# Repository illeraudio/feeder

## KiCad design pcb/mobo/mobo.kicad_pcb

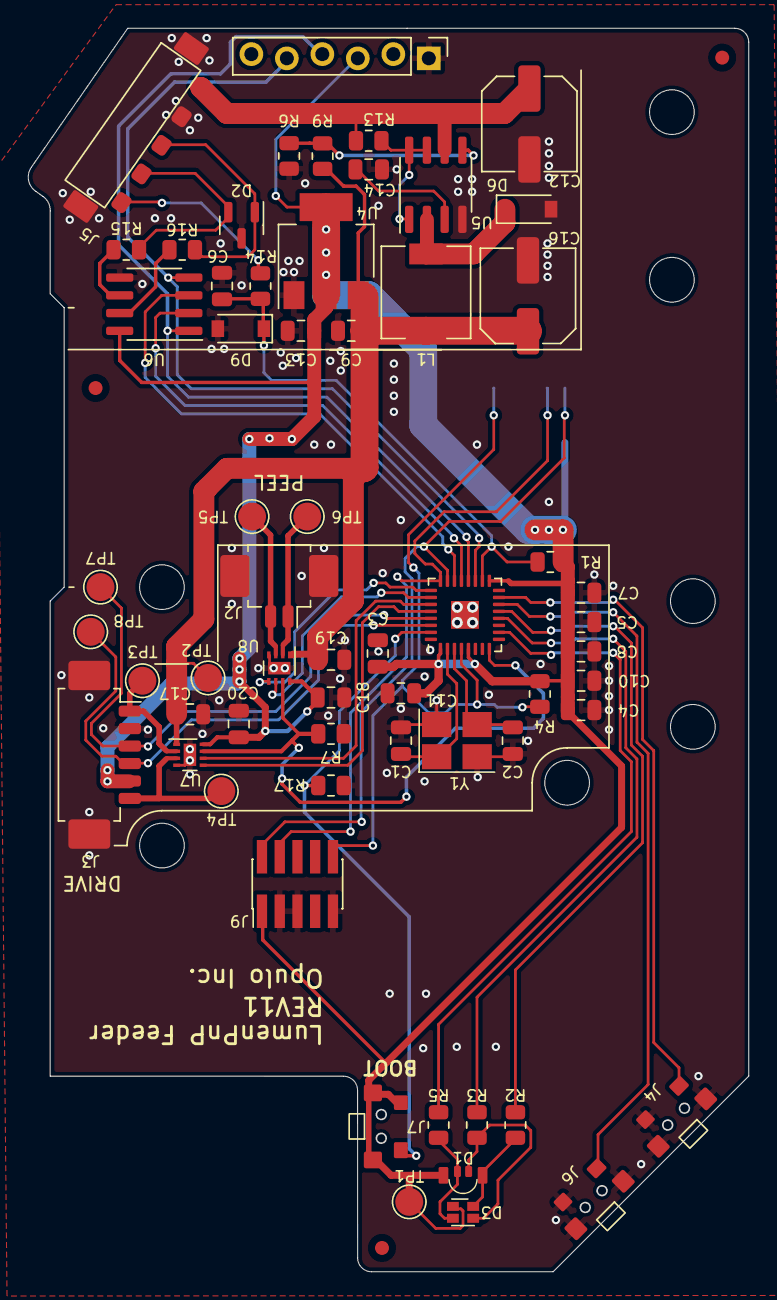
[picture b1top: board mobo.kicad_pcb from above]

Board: 2 copper layers, 51.6 x 89.0 mm, 65 parts (1 on the bottom side), 43 nets.

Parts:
C1, C2: 15p; C_0805_2012Metric
C3, C4, C5, C7, C17, C18, C19, C20: 100n; C_0805_2012Metric
C6: 15pF; C_0805_2012Metric
C8, C10, C11: 4.7uF; C_0805_2012Metric
C9, C13: 10u; C_0805_2012Metric
C12: 100uF; C_Elec_6.3x7.7
C14: 470pF; C_0805_2012Metric
C16: 470uF; C_Elec_6.3x7.7
D1: LED_RGBA; MHS110FRGBCT
D2: SM712_SOT23; SOT-23
D3: LED_RGBA_ALT; LED_LiteOn_LTST-C19HE1WT
D6: 1N5819; D_SOD-123
D9: MMSZ4684T1G; D_SOD-123
FID1, FID2, FID3: Fiducial; Fiducial_1mm_Mask2mm
J1: SWD_10; PinHeader_2x05_P1.27mm_Vertical_SMD
J2: PEEL_MOTOR; Molex_PicoBlade_53261-0271_1x02-1MP_P1.25mm_Horizontal
J3: DRIVE_MOTOR; Molex_PicoBlade_53261-0671_1x06-1MP_P1.25mm_Horizontal
J4, J7: SW1; 1TS003B-1400-3500A-CT
J5: SPRING_FINGERS; AVX-9155-005-541
J6: SW2; 1TS003B-1400-3500A-CT
J8: USART1; UART_FRICTION_FIT
J9: SWD_10; SWD-No-Paste
L1: 220uH; L_6.3x6.3_H3
R1: 1k; R_0805_2012Metric
R2, R3, R5: 470; R_0805_2012Metric
R4, R7, R17: 10K; R_0805_2012Metric
R6: 5.6k; R_0805_2012Metric
R9: 39k; R_0805_2012Metric
R13: 0.33R; R_0805_2012Metric
R14: 220R; R_0805_2012Metric
R15, R16: 20R; R_0805_2012Metric
TP1: TP_3V3; TestPoint_Pad_D2.0mm
TP2: TP_10V; TestPoint_Pad_D2.0mm
TP3: TP_DRIVE_M1; TestPoint_Pad_D2.0mm
TP4: TP_DRIVE_M2; TestPoint_Pad_D2.0mm
TP5: TP_PEEL_M2; TestPoint_Pad_D2.0mm
TP6: TP_PEEL_M1; TestPoint_Pad_D2.0mm
TP7: TP_QUAD_A; TestPoint_Pad_D2.0mm
TP8: TP_QUAD_B; TestPoint_Pad_D2.0mm
U2: STM32F031K6Ux; QFN-32-No-Paste
U4: AP1117-33; SOT-223-3_TabPin2
U5: MC34063AD; SOIC-8_3.9x4.9mm_P1.27mm
U6: MAX3078E; SOIC-8_3.9x4.9mm_P1.27mm
U7, U8: DRV8837; WSON-8-1EP_2x2mm_P0.5mm_EP0.9x1.6mm
Y1: 8MHz; Crystal_SMD_3225-4Pin_3.2x2.5mm_HandSoldering

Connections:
1WIRE: C6.2, D9.1 (K), R1.1, R14.1, U2.18 (PA8)
+3V3: C3.2, C4.2, C5.2, C7.2, C8.2, C10.2, C11.2, C13.1, C18.2, C20.2, D1.1 (RK), D3.4 (A), J1.1 (VTref), J3.5, J7.2, J7.3, J7.4, J8.3, J9.1 (VTref), R1.2, R4.2, TP1.1, U2.1 (VDD), U2.5 (VDDA), U2.17 (VDD), U4.2 (VO), U6.8 (VCC), U7.8 (VCC), U8.8 (VCC)
+10V: C9.1, C16.1, C17.2, C19.2, L1.2, R9.2, TP2.1, U4.3 (VI), U7.1 (VM), U8.1 (VM)
+VDC: C12.1, J5.1, R13.1, U5.6 (Vin)
BOOT0: J7.1, R17.2, U2.31 (BOOT0)
DE: U2.22 (PA12), U6.3 (DE)
DRIVE1: U2.27 (PB4), U7.6 (IN1)
DRIVE2: U2.28 (PB5), U7.5 (IN2)
DRIVE_M1: J3.1, TP3.1, U7.2 (OUT1)
DRIVE_M2: J3.6, TP4.1, U7.3 (OUT2)
DRIVE_QUAD_A: J3.3, TP7.1, U2.29 (PB6)
DRIVE_QUAD_B: J3.4, TP8.1, U2.30 (PB7)
GND: C1.2, C2.2, C3.1, C4.1, C5.1, C6.1, C7.1, C8.1, C9.2, C10.1, C11.1, C12.2, C13.2, C14.1, C16.2, C17.1, C18.1, C19.1, C20.1, D2.3 (common), D6.2 (A), D9.2 (A), J1.3 (GND), J1.5 (GND), J1.9 (GNDDetect), J2.MP, J3.2, J3.MP, J4.2, J4.3, J4.4, J5.2, J5.6, J5.7, J6.2, J6.3, J6.4, J8.1, J9.3 (GND), J9.5 (GND), J9.9 (GNDDetect), R6.2, R7.1, R17.1, U2.33 (VSS), U4.1 (GND), U5.4 (GND), U6.5 (GND), U7.4 (GND), U7.9 (GND), U8.4 (GND), U8.9 (GND), Y1.2, Y1.4
LED_B: R5.1, U2.10 (PA4)
LED_G: R3.1, U2.12 (PA6)
LED_R: R2.1, U2.13 (PA7)
MCU_RX: J8.4, U2.20 (PA10), U6.1 (RO)
MCU_TX: J8.5, U2.19 (PA9), U6.4 (DI)
MOTOR_ENABLE: R7.2, U2.8 (PA2), U7.7 (~SLEEP), U8.7 (~SLEEP)
unnamed: C14.2, U5.3 (TC)
unnamed: D1.2 (GK), D3.3 (BK), R5.2
unnamed: D1.3 (BK), D3.2 (GK), R3.2
unnamed: D1.4 (A), D3.1 (RK), R2.2
unnamed: D6.1 (K), L1.1, U5.2 (SwE)
unnamed: J5.5, R14.2
unnamed: R6.1, R9.1, U5.5 (Vfb)
unnamed: R13.2, U5.1 (SwC), U5.7 (Ipk), U5.8 (DC)
unnamed: R15.1, U6.6 (A)
unnamed: R16.1, U6.7 (B)
OSC_IN: C1.1, U2.2 (PF0), Y1.1
OSC_OUT: C2.1, U2.3 (PF1), Y1.3
PEEL1: U2.26 (PB3), U8.6 (IN1)
PEEL2: U2.25 (PA15), U8.5 (IN2)
PEEL_M1: J2.1, TP6.1, U8.2 (OUT1)
PEEL_M2: J2.2, TP5.1, U8.3 (OUT2)
RESET: J1.10 (~RESET), J9.10 (~RESET), R4.1, U2.4 (NRST)
RS-485+: D2.2 (A2), J5.4, R15.2
RS-485-: D2.1 (A1), J5.3, R16.2
SW1: J4.1, U2.15 (PB1)
SW2: J6.1, U2.14 (PB0)
SWCLK: J1.4 (SWDCLK/TCK), J9.4 (SWDCLK/TCK), U2.24 (PA14)
SWDIO: J1.2 (SWDIO/TMS), J9.2 (SWDIO/TMS), U2.23 (PA13)
~RE: U2.21 (PA11), U6.2 (~RE)

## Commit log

2025-07-22 tidy pcb. 3dprinted jigs.
2025-07-27 openpnp config.
2025-07-28 indexing-wheel milled brass
2025-08-04 update openpnp config
